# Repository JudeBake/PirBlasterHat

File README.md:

# PirBlasterHat
Raspberry Pi IR Blaster Hat

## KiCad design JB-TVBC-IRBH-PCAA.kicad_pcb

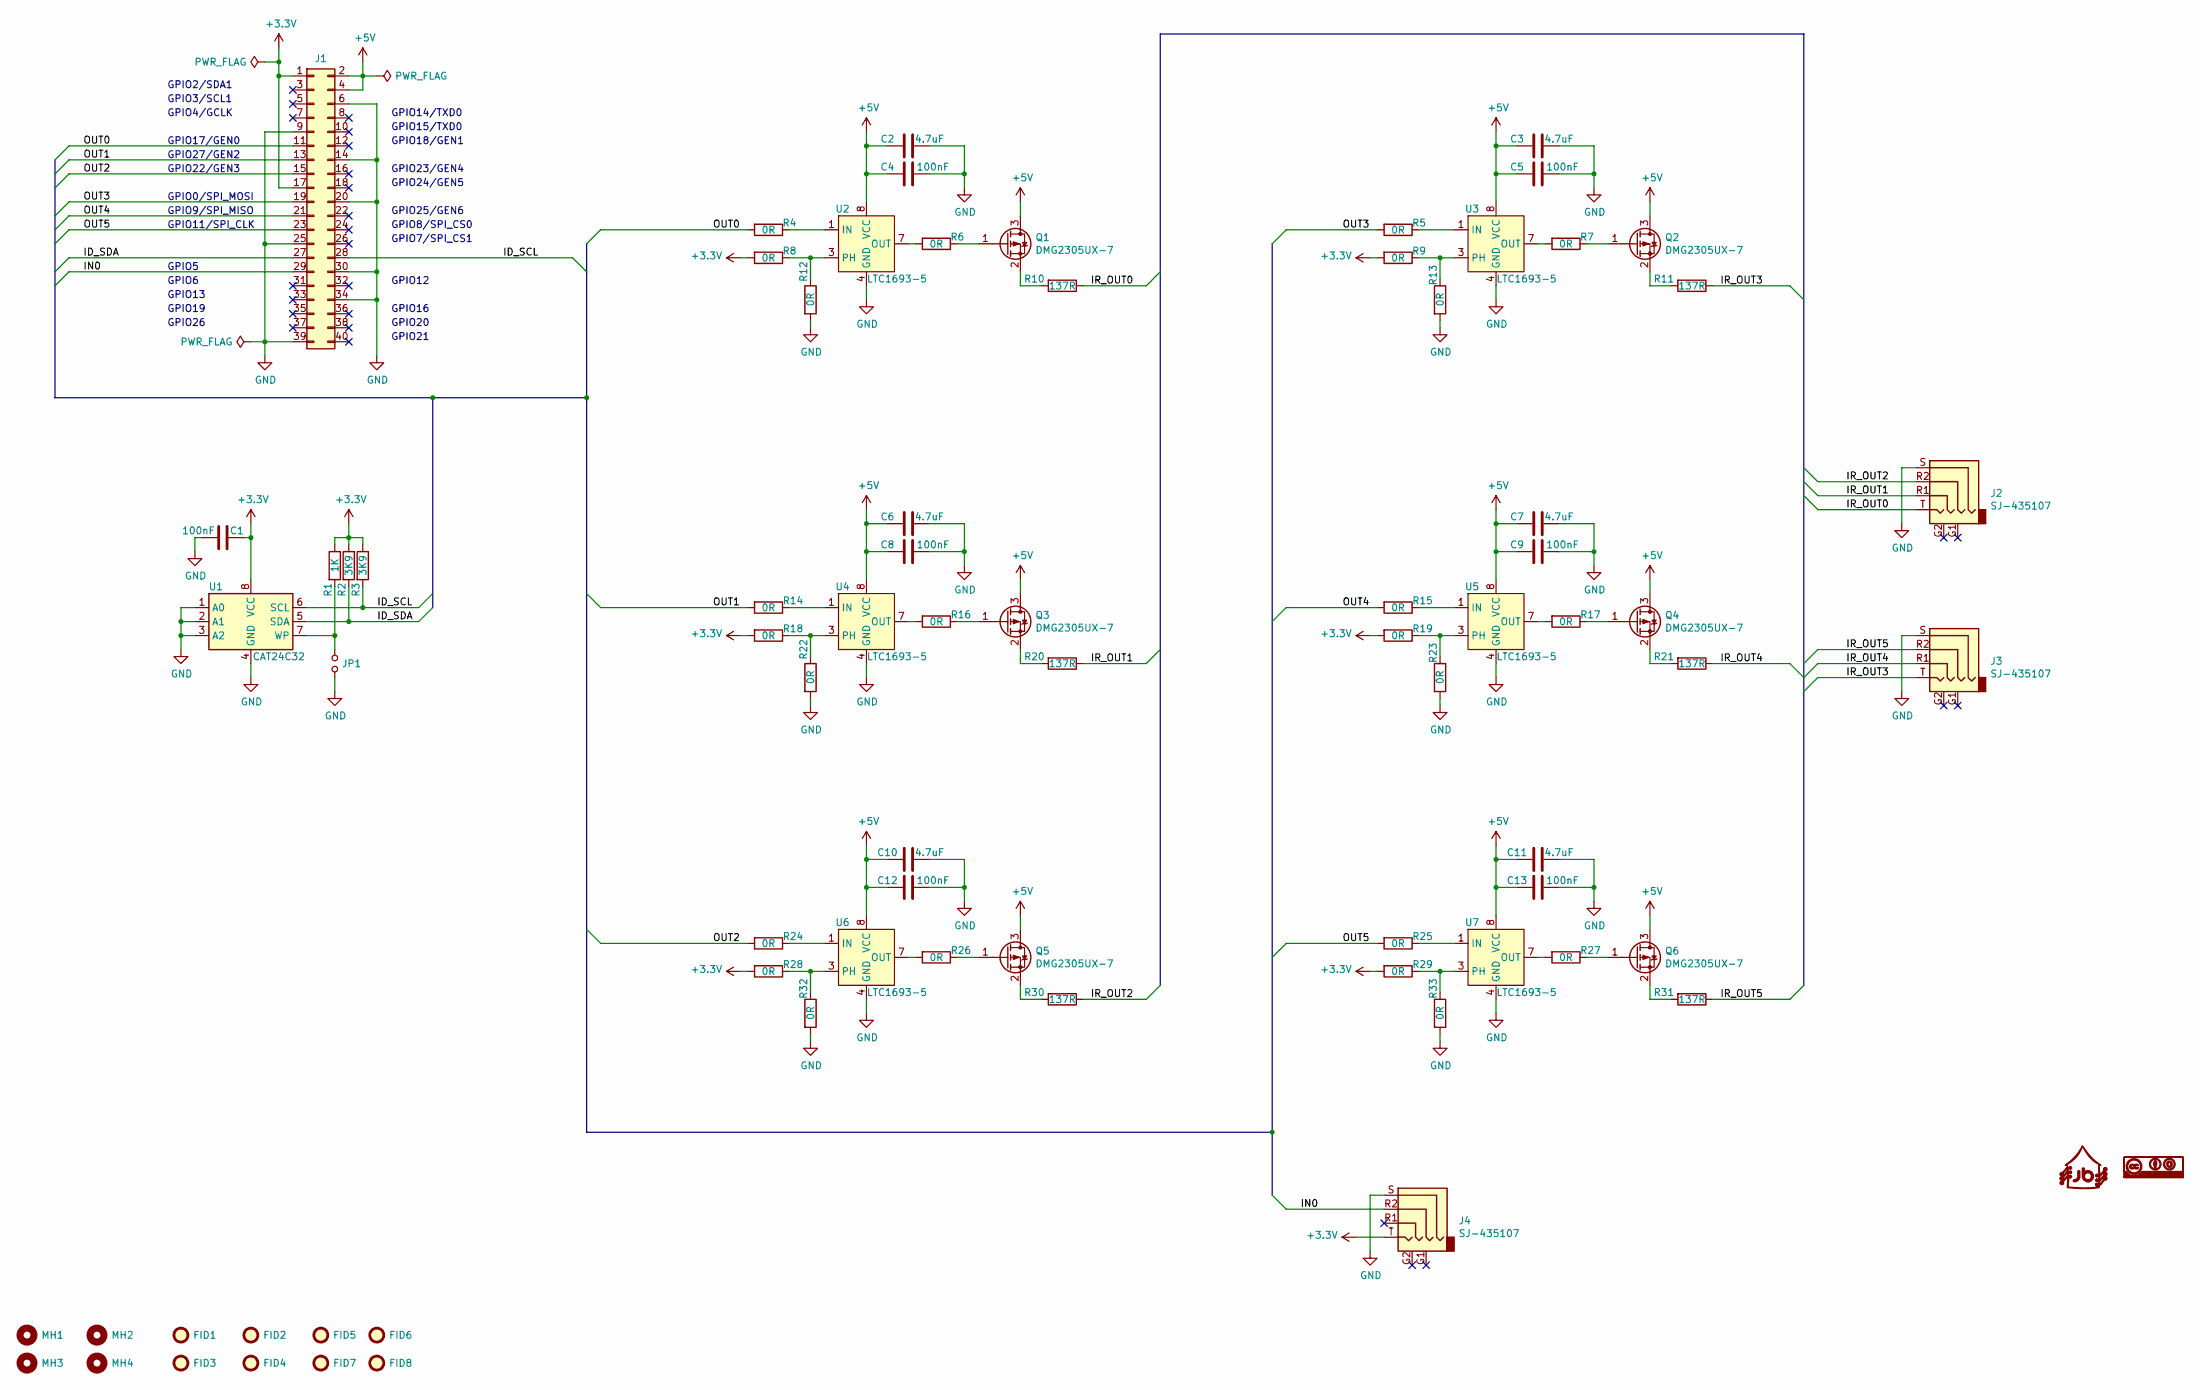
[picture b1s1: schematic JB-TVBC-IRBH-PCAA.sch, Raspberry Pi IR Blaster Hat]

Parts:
C1, C4, C5, C8, C9, C12, C13: 100nF_CER_0603_50V; C_0603_1608Metric_Pad1.05x0.95mm_HandSolder; Manufacturer Part Number 06033D104MAT2A; Digi-Key Part Number 478-7905-2-ND
C2, C3, C6, C7, C10, C11: 4.7uF_CER_0805_16V; C_0805_2012Metric_Pad1.15x1.40mm_HandSolder; Manufacturer Part Number CL21B475KOFNNNE; Digi-Key Part Number 1276-2873-2-ND
FID1, FID2, FID3, FID4, FID5, FID6, FID7, FID8: Fiducial; Fiducial_1.5mm_Mask3mm
G1: JudeBake_Logo; JB_Logo_10MM
G2: CC-BY-SA_Logo; CC-BY-SA_10MM
J1: CONN_2x20_FEM_100PITCH_635INS_280POST; ESQ-120-34-G-D; Manufacturer Part Number ESQ-120-34-G-D; Digi-Key Part Number SAM9319-ND
J2, J3, J4: SJ-435107; Manufacturer Part Number SJ-435107; Digi-Key Part Number CP-435107-ND
JP1: Solder_Jumper_1.3MM; SolderJumper-2_P1.3mm_Open_RoundedPad1.0x1.5mm
MH1, MH2, MH3, MH4: MH-NPLTD-M2.5; MountingHole_2.7mm_M2.5_DIN965
Q1, Q2, Q3, Q4, Q5, Q6: DMG2305UX-7; SOT-23_Handsoldering; Manufacturer Part Number DMG2305UX-7; Digi-Key Part Number DMG2305UX-7DICT-ND
R1: 1K_0603_100MW; R_0603_1608Metric_Pad1.05x0.95mm_HandSolder; Manufacturer Part Number ERJ-3EKF1001V; Digi-Key Part Number P1.00KHCT-ND
R2, R3: 3K9_0603_100MW; R_0603_1608Metric_Pad1.05x0.95mm_HandSolder; Manufacturer Part Number RC0603FR-073K9L; Digi-Key Part Number 311-3.90KHRCT-ND
R4, R5, R6, R7, R8, R9, R12, R13, R14, R15, R16, R17, R18, R19, R22, R23, R24, R25, R26, R27, R28, R29, R32, R33: 0R_0603_100MW; R_0603_1608Metric_Pad1.05x0.95mm_HandSolder; Manufacturer Part Number ERJ-3GEY0R00V; Digi-Key Part Number P0.0GTR-ND
R10, R11, R20, R21, R30, R31: 137R_1206_250MW; R_1206_3216Metric_Pad1.42x1.75mm_HandSolder; Manufacturer Part Number CRCW1206137RFKEA; Digi-Key Part Number 541-137FCT-ND
U1: CAT24C32; SOIC-8_3.9x4.9mm_P1.27mm; Manufacturer Part Number CAT24C32WI-GT3; Digi-Key Part Number CAT24C32WI-GT3CT-ND
U2, U3, U4, U5, U6, U7: LTC1693-5; MSOP-8_3x3mm_P0.65mm; Manufacturer Part Number LTC1693-5CMS8#PBF; Digi-Key Part Number LTC1693-5CMS8#PBF-ND

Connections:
+3V3: C1.1, J1.1, J1.17, J4.T, R1.1, R2.1, R3.1, R8.2, R9.2, R18.2, R19.2, R28.2, R29.2, U1.8 (VCC)
+5V: C2.2, C3.2, C4.2, C5.2, C6.2, C7.2, C8.2, C9.2, C10.2, C11.2, C12.2, C13.2, J1.2, J1.4, Q1.3 (D), Q2.3 (D), Q3.3 (D), Q4.3 (D), Q5.3 (D), Q6.3 (D), U2.8 (VCC), U3.8 (VCC), U4.8 (VCC), U5.8 (VCC), U6.8 (VCC), U7.8 (VCC)
/ID_SCL: J1.28, R3.2, U1.6 (SCL)
/ID_SDA: J1.27, R2.2, U1.5 (SDA)
/IN0: J1.29, J4.R2
/IR_OUT0: J2.T, R10.1
/IR_OUT1: J2.R1, R20.1
/IR_OUT2: J2.R2, R30.1
/IR_OUT3: J3.T, R11.1
/IR_OUT4: J3.R1, R21.1
/IR_OUT5: J3.R2, R31.1
/OUT0: J1.11, R4.2
/OUT1: J1.13, R14.2
/OUT2: J1.15, R24.2
/OUT3: J1.19, R5.2
/OUT4: J1.21, R15.2
/OUT5: J1.23, R25.2
GND: C1.2, C2.1, C3.1, C4.1, C5.1, C6.1, C7.1, C8.1, C9.1, C10.1, C11.1, C12.1, C13.1, J1.6, J1.9, J1.14, J1.20, J1.25, J1.30, J1.34, J1.39, J2.S, J3.S, J4.S, JP1.2, R12.2, R13.2, R22.2, R23.2, R32.2, R33.2, U1.1 (A0), U1.2 (A1), U1.3 (A2), U1.4 (GND), U2.4 (GND), U3.4 (GND), U4.4 (GND), U5.4 (GND), U6.4 (GND), U7.4 (GND)
unnamed: JP1.1, R1.2, U1.7 (WP)
unnamed: Q1.1 (G), R6.1
unnamed: Q1.2 (S), R10.2
unnamed: Q2.1 (G), R7.1
unnamed: Q2.2 (S), R11.2
unnamed: Q3.1 (G), R16.1
unnamed: Q3.2 (S), R20.2
unnamed: Q4.1 (G), R17.1
unnamed: Q4.2 (S), R21.2
unnamed: Q5.1 (G), R26.1
unnamed: Q5.2 (S), R30.2
unnamed: Q6.1 (G), R27.1
unnamed: Q6.2 (S), R31.2
unnamed: R4.1, U2.1 (IN)
unnamed: R5.1, U3.1 (IN)
unnamed: R6.2, U2.7 (OUT)
unnamed: R7.2, U3.7 (OUT)
unnamed: R8.1, R12.1, U2.3 (PH)
unnamed: R9.1, R13.1, U3.3 (PH)
unnamed: R14.1, U4.1 (IN)
unnamed: R15.1, U5.1 (IN)
unnamed: R16.2, U4.7 (OUT)
unnamed: R17.2, U5.7 (OUT)
unnamed: R18.1, R22.1, U4.3 (PH)
unnamed: R19.1, R23.1, U5.3 (PH)
unnamed: R24.1, U6.1 (IN)
unnamed: R25.1, U7.1 (IN)
unnamed: R26.2, U6.7 (OUT)
unnamed: R27.2, U7.7 (OUT)
unnamed: R28.1, R32.1, U6.3 (PH)
unnamed: R29.1, R33.1, U7.3 (PH)

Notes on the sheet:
GPIO2/SDA1
GPIO3/SCL1
GPIO4/GCLK
GPIO17/GEN0
GPIO27/GEN2
GPIO22/GEN3
GPIO0/SPI_MOSI
GPIO9/SPI_MISO
GPIO11/SPI_CLK
GPIO5
GPIO6
GPIO13
GPIO19
GPIO26
GPIO14/TXD0
GPIO15/TXD0
GPIO18/GEN1
GPIO23/GEN4
GPIO24/GEN5
GPIO25/GEN6
GPIO8/SPI_CS0
GPIO7/SPI_CS1
GPIO12
GPIO16
GPIO20
GPIO21

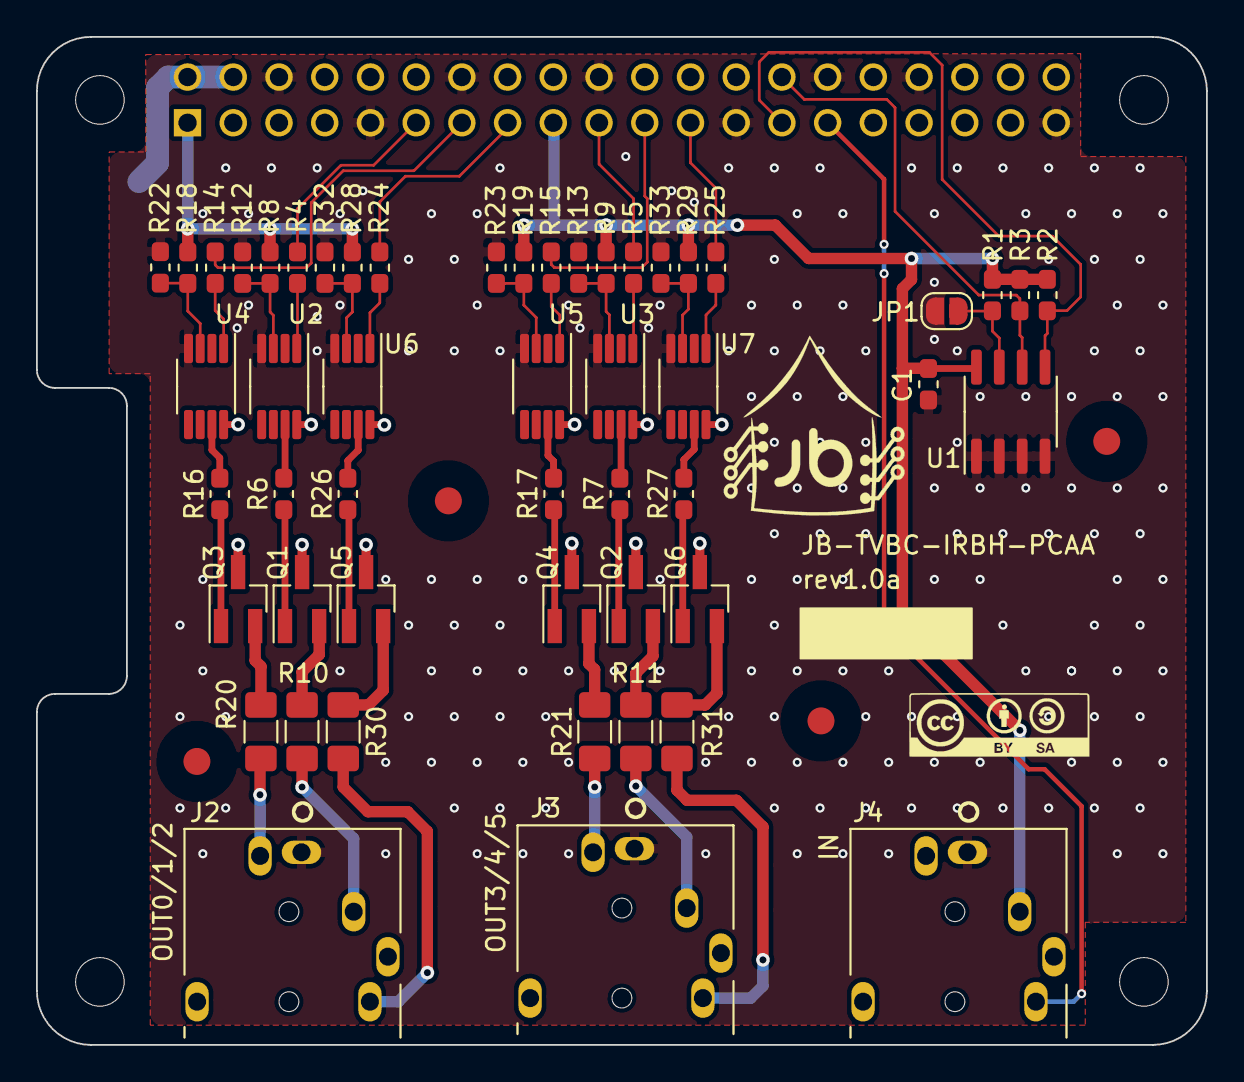
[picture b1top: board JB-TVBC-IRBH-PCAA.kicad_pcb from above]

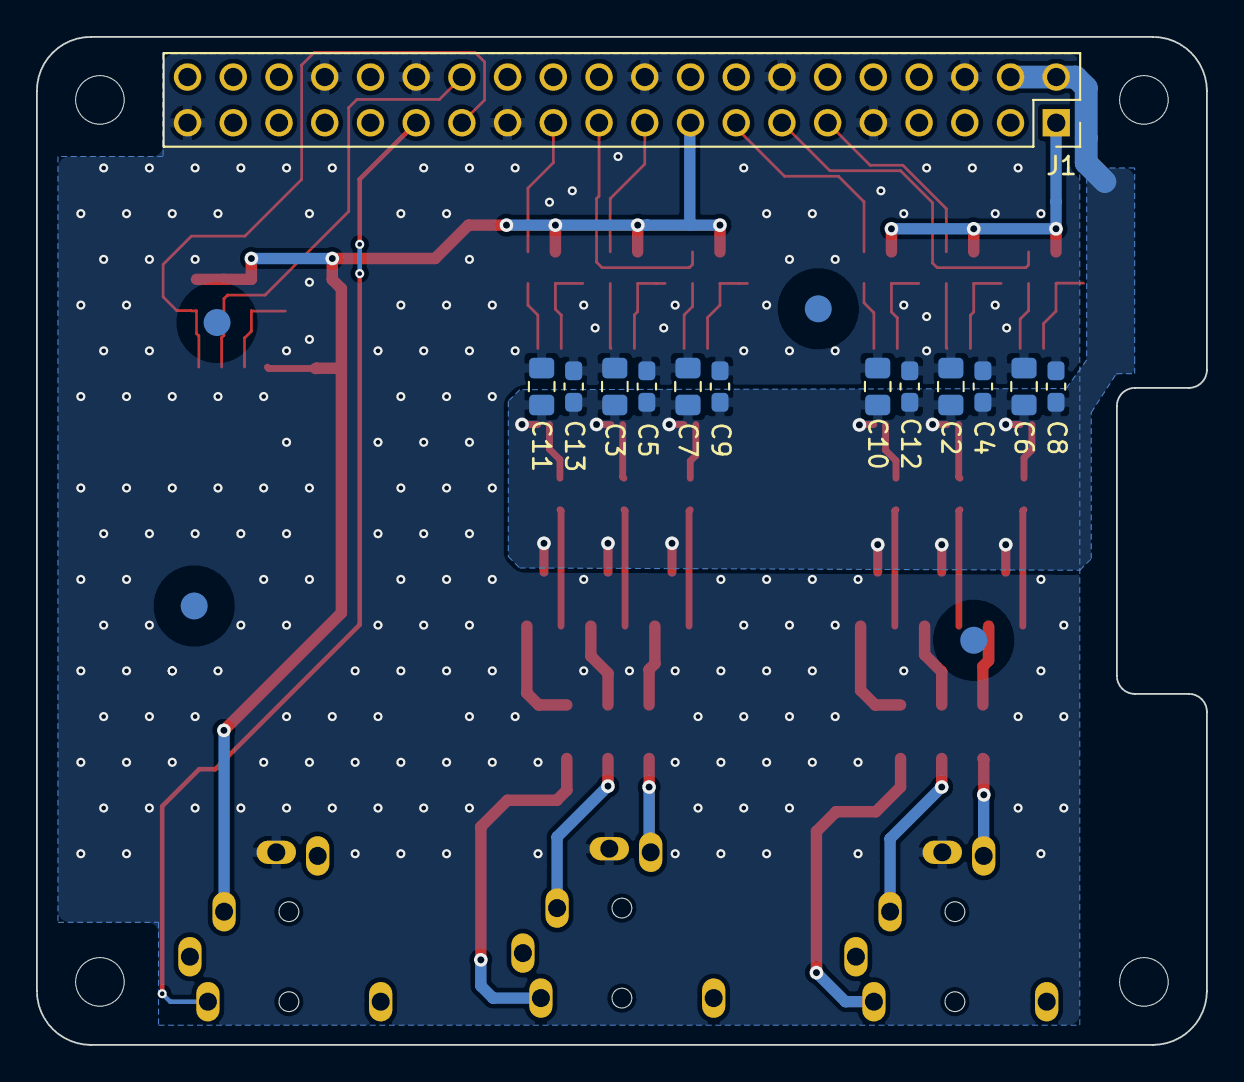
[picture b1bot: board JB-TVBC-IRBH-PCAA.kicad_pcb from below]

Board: 2 copper layers, 65.0 x 56.0 mm, 78 parts (17 on the bottom side), 49 nets.

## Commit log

2020-03-08 project creation
2020-03-15 WIP. need to remove pull-up on PHASE and add pull-down on IN (gate driver
2020-03-15 adding fiducial + graphics symbol
2020-03-15 adding jack legend on silkscreen
2020-03-15 saved
